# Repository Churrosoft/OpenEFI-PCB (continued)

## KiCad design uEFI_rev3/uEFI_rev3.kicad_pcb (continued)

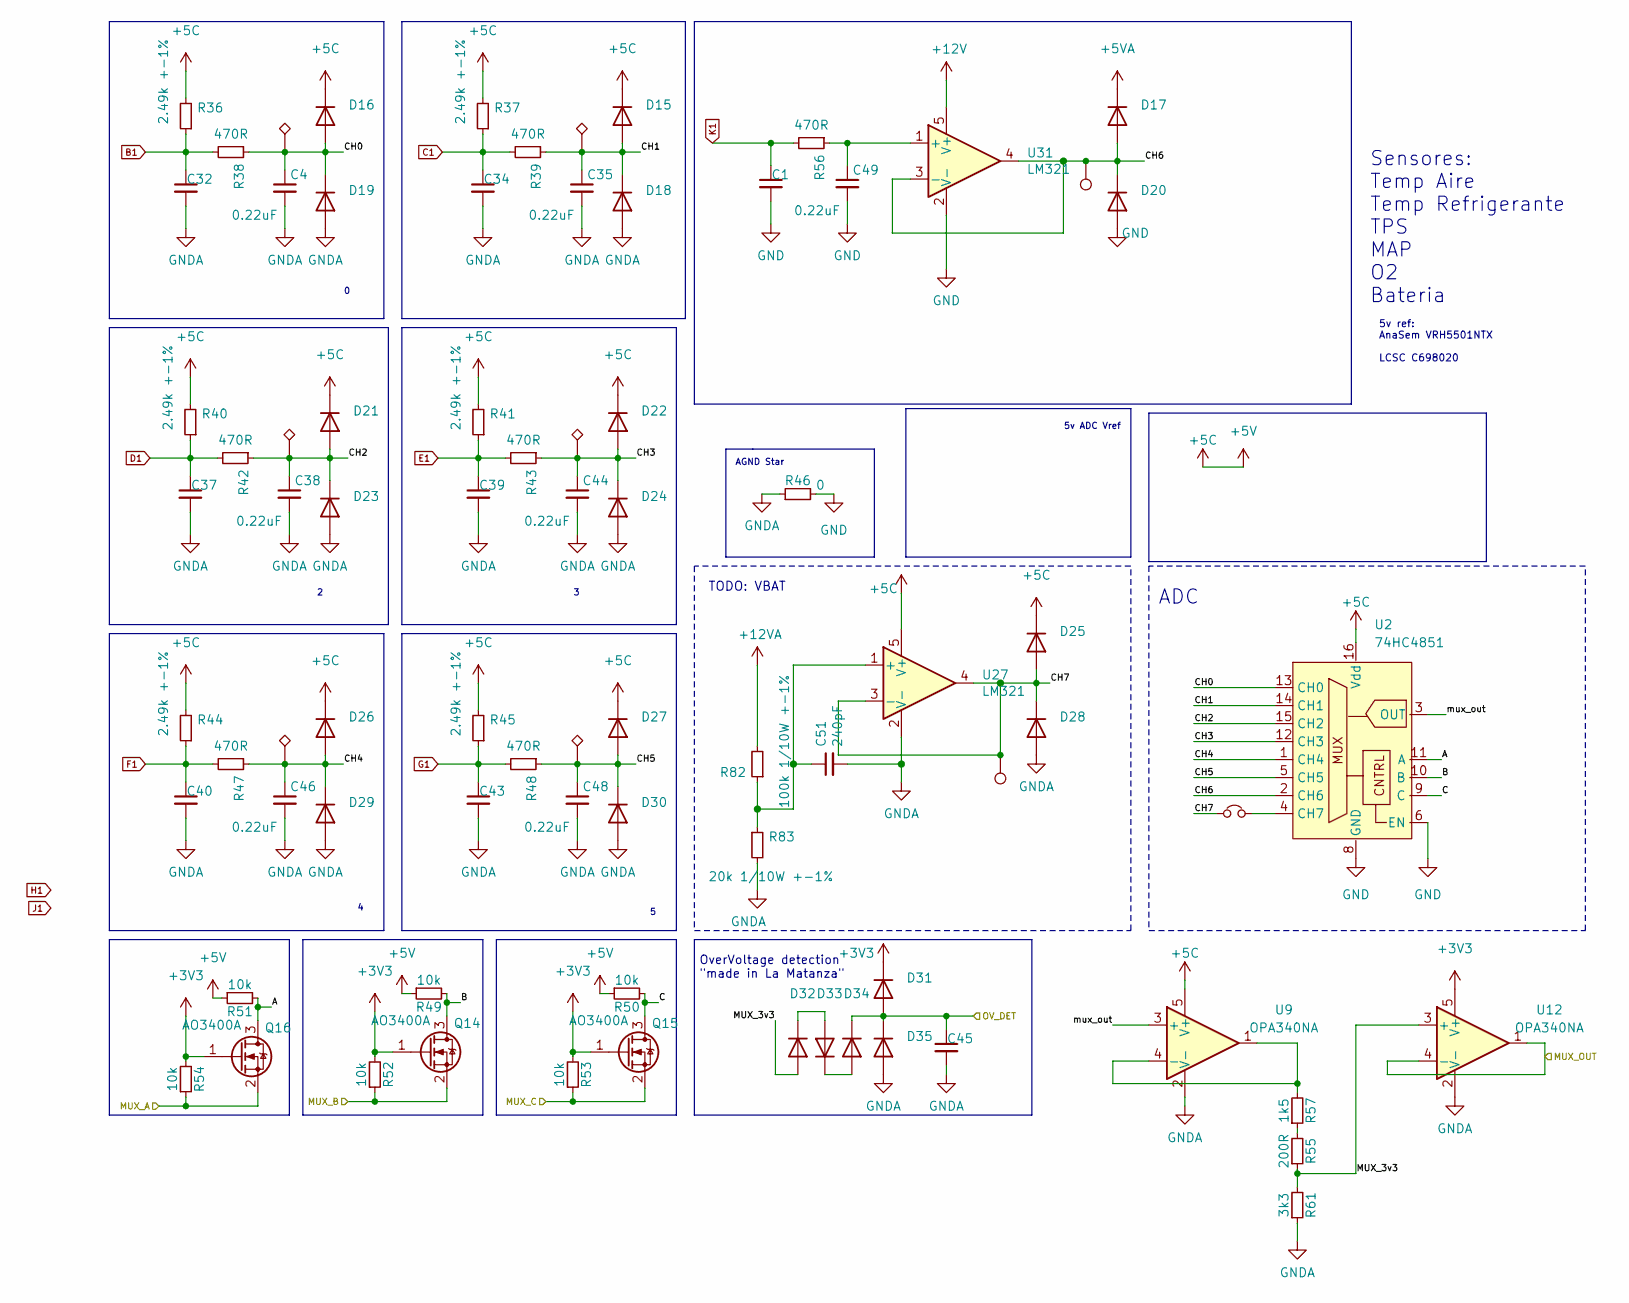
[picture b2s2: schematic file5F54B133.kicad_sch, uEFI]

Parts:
C1, C32, C34, C37, C39, C40, C43, C45: 100nF; C_0805_2012Metric; LCSC C49678
C4, C35, C38, C44, C46, C48, C49: 0.22uF; C_0603_1608Metric
C51: 240pF; C_0603_1608Metric; LCSC C185593
D15, D16, D17, D18, D19, D20, D21, D22, D23, D24, D25, D26, D27, D28, D29, D30, D31, D32, D33, D34, D35: K26; D_SOD-323; LCSC C2922179
JP12: Jumper_NC_Small; SolderJumper-2_P1.3mm_Open_TrianglePad1.0x1.5mm
Q14, Q15, Q16: AO3400A; SOT-23; LCSC C347475
R36, R37, R40, R41, R44, R45: 2.49k +-1%; R_0603_1608Metric
R38, R39, R42, R43, R47, R48, R56: 470R; R_0603_1608Metric
R46: 0; R_0603_1608Metric
R49, R50, R51, R52, R53, R54: 10k; R_0603_1608Metric
R55: 200R; R_0603_1608Metric
R57: 1k5; R_0603_1608Metric
R61: 3k3; R_0603_1608Metric
R82: 100k 1/10W +-1%; R_0603_1608Metric; LCSC C217840
R83: 20k 1/10W +-1%; R_0603_1608Metric
TP10, TP11, TP12, TP13, TP14, TP15: TestPoint_Alt; TestPoint_THTPad_1.0x1.0mm_Drill0.5mm
TP18, TP19: TestPoint; TestPoint_Pad_2.0x2.0mm
U2: 74HC4851; SOIC-16_3.9x9.9mm_P1.27mm; LCSC C233468
U9, U12: OPA340NA; SOT-23-5
U27, U31: LM321; SOT-23-5

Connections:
+5C: D15.1 (K), D16.1 (K), D21.1 (K), D22.1 (K), D25.1 (K), D26.1 (K), D27.1 (K), R36.2, R37.2, R40.2, R41.2, R44.2, R45.2, R49.1, R50.1, R51.1, U2.16 (Vdd), U9.5 (V+), U27.5 (V+); also elsewhere on the board
+5VA: D17.1 (K); also elsewhere on the board
+12V: U31.5 (V+); also elsewhere on the board
+12VA: R82.2; also elsewhere on the board
/MUX_A: Q16.2 (S), R54.1; also elsewhere on the board
/MUX_B: Q14.2 (S), R52.1; also elsewhere on the board
/MUX_C: Q15.2 (S), R53.1; also elsewhere on the board
/MUX_OUT: U12.1, U12.4 (-); also elsewhere on the board
/Sensores/A: Q16.3 (D), R51.2, U2.11 (A)
/Sensores/B: Q14.3 (D), R49.2, U2.10 (B)
/Sensores/C: Q15.3 (D), R50.2, U2.9 (C)
/Sensores/CH0: C4.1, D16.2 (A), D19.1 (K), R38.1, TP10.1, U2.13 (CH0)
/Sensores/CH1: C35.1, D15.2 (A), D18.1 (K), R39.1, TP11.1, U2.14 (CH1)
/Sensores/CH2: C38.1, D21.2 (A), D23.1 (K), R42.1, TP12.1, U2.15 (CH2)
/Sensores/CH3: C44.1, D22.2 (A), D24.1 (K), R43.1, TP13.1, U2.12 (CH3)
/Sensores/CH4: C46.1, D26.2 (A), D29.1 (K), R47.1, TP14.1, U2.1 (CH4)
/Sensores/CH5: C48.1, D27.2 (A), D30.1 (K), R48.1, TP15.1, U2.5 (CH5)
/Sensores/CH6: D17.2 (A), D20.1 (K), TP18.1, U2.2 (CH6), U31.3 (-), U31.4
/Sensores/CH7: D25.2 (A), D28.1 (K), JP12.1, TP19.1, U27.3 (-), U27.4
/Sensores/MUX_3v3: D32.2 (A), R55.1, R61.2, U12.3 (+)
/Sensores/mux_out: U2.3 (OUT), U9.3 (+)
B1: C32.1, R36.1, R38.2; also elsewhere on the board
C1: C34.1, R37.1, R39.2; also elsewhere on the board
D1: C37.1, R40.1, R42.2; also elsewhere on the board
E1: C39.1, R41.1, R43.2; also elsewhere on the board
F1: C40.1, R44.1, R47.2; also elsewhere on the board
G1: C43.1, R45.1, R48.2; also elsewhere on the board
GND: C1.2, C49.2, D20.2 (A), R46.2, U2.6 (EN), U2.8 (GND), U31.2 (V-); also elsewhere on the board
GNDA: C4.2, C32.2, C34.2, C35.2, C37.2, C38.2, C39.2, C40.2, C43.2, C44.2, C45.2, C46.2, C48.2, C51.2, D18.2 (A), D19.2 (A), D23.2 (A), D24.2 (A), D28.2 (A), D29.2 (A), D30.2 (A), D35.2 (A), R46.1, R61.1, R83.2, U9.2 (V-), U12.2 (V-), U27.2 (V-)
K1: C1.1, R56.2; also elsewhere on the board
unnamed: C45.1, D31.2 (A), D34.1 (K), D35.1 (K)
unnamed: C49.1, R56.1, U31.1 (+)
unnamed: C51.1, R82.1, R83.1, U27.1 (+)
unnamed: D32.1 (K), D33.2 (A)
unnamed: D33.1 (K), D34.2 (A)
unnamed: JP12.2, U2.4 (CH7)
unnamed: R55.2, R57.1
unnamed: R57.2, U9.1, U9.4 (-)

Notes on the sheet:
TODO: VBAT
Sensores: Temp Aire Temp Refrigerante TPS MAP O2 Bateria
OverVoltage detection "made in La Matanza"
ADC
5v ADC Vref
5v ref: AnaSem VRH5501NTX LCSC C698020
AGND Star

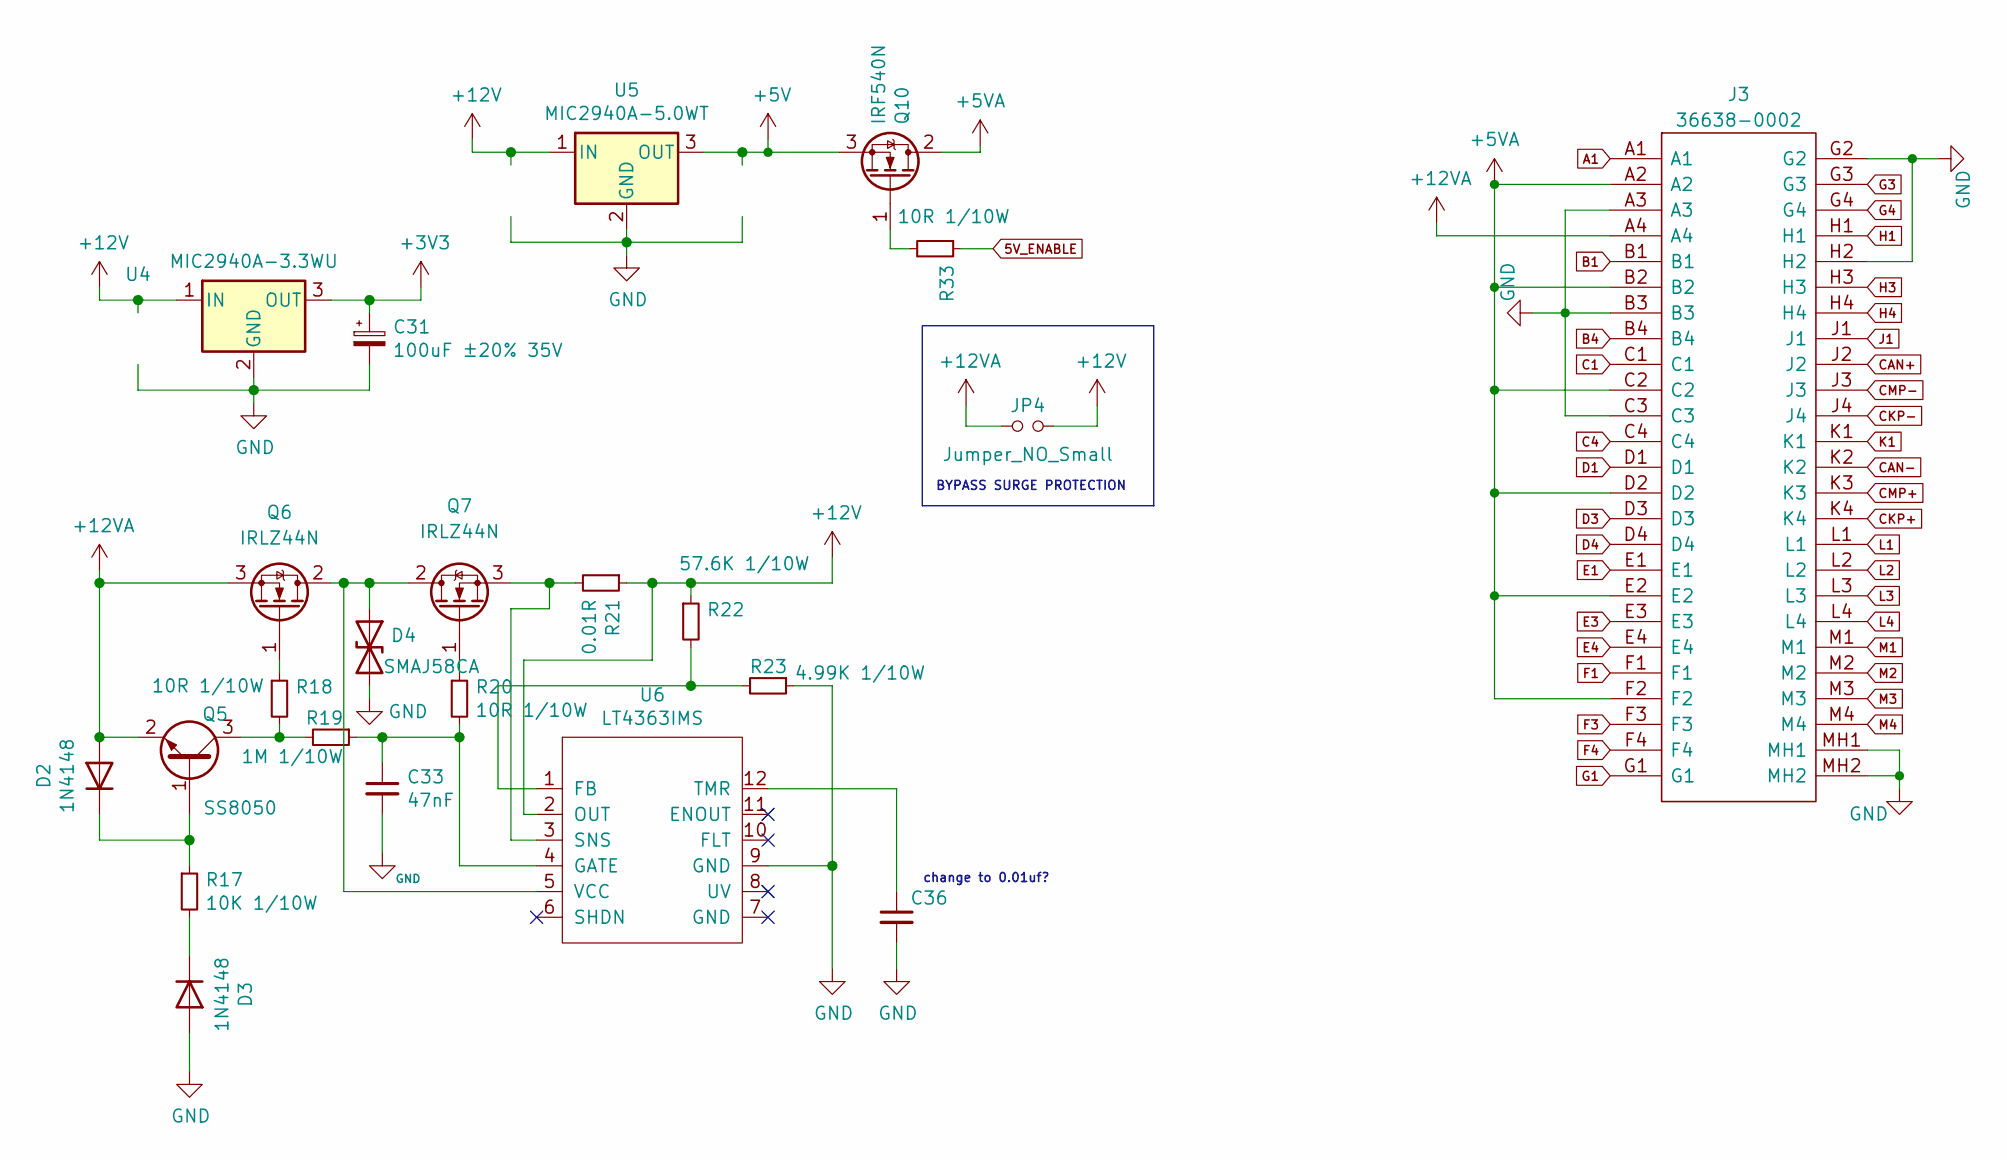
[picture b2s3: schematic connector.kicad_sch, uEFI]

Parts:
C31: 100uF ±20% 35V; CP_Elec_6.3x7.7; LCSC C141427
C33: 47nF; C_0603_1608Metric
C36: 100nF; C_0805_2012Metric; LCSC C49678
D2, D3: 1N4148; D_SOD-523; LCSC C511874
D4: SMAJ58CA; D_SMA
J3: 36638-0002; 366380002; Manufacturer_Part_Number 36638-0002; Mouser Part Number 538-36638-0002
JP4: Jumper_NO_Small; SolderJumper-2_P1.3mm_Open_RoundedPad1.0x1.5mm
Q5: SS8050; SOT-23; LCSC C2150
Q6, Q7: IRLZ44N; TO-220-3_Vertical
Q10: IRF540N; TO-220-3_Vertical
R17: 10K 1/10W; R_0603_1608Metric
R18, R20, R33: 10R 1/10W; R_0603_1608Metric
R19: 1M 1/10W; R_0603_1608Metric
R21: 0.01R; R_1210_3225Metric; LCSC C175884
R22: 57.6K 1/10W; R_0603_1608Metric
R23: 4.99K 1/10W; R_0603_1608Metric
U4: MIC2940A-3.3WU; TO-263-3_TabPin2
U5: MIC2940A-5.0WT; TO-220-3_Vertical
U6: LT4363IMS; MSOP-12_3x4mm_P0.65mm

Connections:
5V_ENABLE: R33.1; also elsewhere on the board
+5C: Q10.3 (S), U5.3 (OUT); also elsewhere on the board
+5VA: J3.A2, J3.B2, J3.C2, J3.D2, J3.E2, J3.F2, Q10.2 (D); also elsewhere on the board
+12V: JP4.2, R21.1, R22.1, U4.1 (IN), U5.1 (IN), U6.2 (OUT); also elsewhere on the board
+12VA: D2.2 (A), J3.A4, JP4.1, Q5.2 (E), Q6.3 (S); also elsewhere on the board
A1: J3.A1; also elsewhere on the board
B1: J3.B1; also elsewhere on the board
B4: J3.B4; also elsewhere on the board
C1: J3.C1; also elsewhere on the board
C4: J3.C4; also elsewhere on the board
CAN+: J3.J2; also elsewhere on the board
CAN-: J3.K2; also elsewhere on the board
CKP+: J3.K4; also elsewhere on the board
CKP-: J3.J4; also elsewhere on the board
CMP+: J3.K3; also elsewhere on the board
CMP-: J3.J3; also elsewhere on the board
D1: J3.D1; also elsewhere on the board
D3: J3.D3; also elsewhere on the board
D4: J3.D4; also elsewhere on the board
E1: J3.E1; also elsewhere on the board
E3: J3.E3; also elsewhere on the board
E4: J3.E4; also elsewhere on the board
F1: J3.F1; also elsewhere on the board
F3: J3.F3; also elsewhere on the board
F4: J3.F4; also elsewhere on the board
G1: J3.G1; also elsewhere on the board
G3: J3.G3; also elsewhere on the board
G4: J3.G4; also elsewhere on the board
GND: C31.2, C33.2, C36.2, D3.2 (A), D4.2 (A2), J3.A3, J3.B3, J3.C3, J3.G2, J3.H2, J3.MH1, J3.MH2, R23.1, U4.2 (GND), U5.2 (GND), U6.9 (GND); also elsewhere on the board
H1: J3.H1; also elsewhere on the board
H3: J3.H3; also elsewhere on the board
H4: J3.H4; also elsewhere on the board
J1: J3.J1
K1: J3.K1; also elsewhere on the board
L1: J3.L1; also elsewhere on the board
L2: J3.L2; also elsewhere on the board
L3: J3.L3; also elsewhere on the board
L4: J3.L4; also elsewhere on the board
M1: J3.M1; also elsewhere on the board
M2: J3.M2; also elsewhere on the board
M3: J3.M3; also elsewhere on the board
M4: J3.M4; also elsewhere on the board
unnamed: C33.1, R19.1, R20.2, U6.4 (GATE)
unnamed: C36.1, U6.12 (TMR)
unnamed: D2.1 (K), Q5.1 (B), R17.1
unnamed: D3.1 (K), R17.2
unnamed: D4.1 (A1), Q6.2 (D), Q7.2 (D), U6.5 (VCC)
unnamed: Q5.3 (C), R18.2, R19.2
unnamed: Q6.1 (G), R18.1
unnamed: Q7.1 (G), R20.1
unnamed: Q7.3 (S), R21.2, U6.3 (SNS)
unnamed: Q10.1 (G), R33.2
unnamed: R22.2, R23.2, U6.1 (FB)

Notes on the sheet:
BYPASS SURGE PROTECTION
change to 0.01uf?

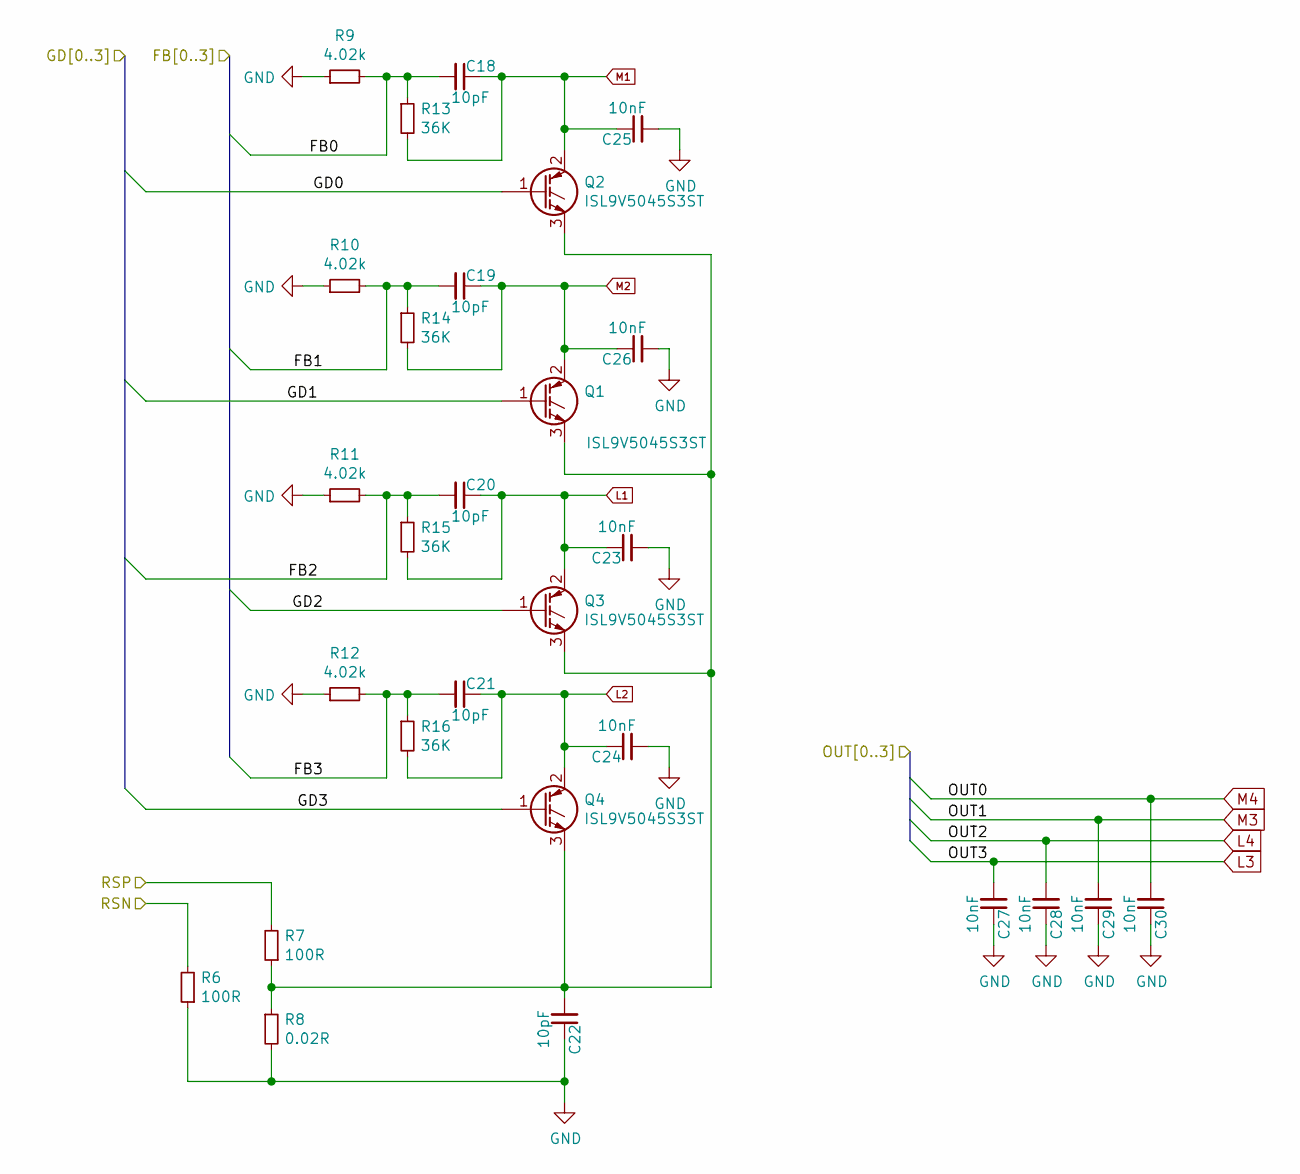
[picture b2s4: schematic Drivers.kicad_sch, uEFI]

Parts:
C18, C19, C20, C21: 10pF; C_0603_1608Metric; LCSC C106245
C22: 10pF; C_0603_1608Metric
C23, C24, C25, C26, C27, C28, C29, C30: 10nF; C_0603_1608Metric; LCSC C100042
Q1, Q2, Q3, Q4: ISL9V5045S3ST; TO-263-2
R6, R7: 100R; R_0603_1608Metric; LCSC C159890
R8: 0.02R; R_2512_6332Metric; LCSC C326611
R9, R10, R11, R12: 4.02k; R_0603_1608Metric; LCSC C23040
R13, R14, R15, R16: 36K; R_0603_1608Metric; LCSC C192548

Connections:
/RSN: R6.2; also elsewhere on the board
/RSP: R7.2; also elsewhere on the board
/Sheet5FA9324A/FB0: C18.2, R9.2, R13.1; also elsewhere on the board
/Sheet5FA9324A/FB1: C19.2, R10.2, R14.1; also elsewhere on the board
/Sheet5FA9324A/FB2: C20.2, R11.2, R15.1; also elsewhere on the board
/Sheet5FA9324A/FB3: C21.2, R12.2, R16.1; also elsewhere on the board
/Sheet5FA9324A/GD0: Q2.1 (G); also elsewhere on the board
/Sheet5FA9324A/GD1: Q1.1 (G); also elsewhere on the board
/Sheet5FA9324A/GD2: Q3.1 (G); also elsewhere on the board
/Sheet5FA9324A/GD3: Q4.1 (G); also elsewhere on the board
GND: C22.1, C23.2, C24.2, C25.2, C26.2, C27.1, C28.1, C29.1, C30.1, R6.1, R8.2, R9.1, R10.1, R11.1, R12.1; also elsewhere on the board
L1: C20.1, C23.1, Q3.2 (C), R15.2; also elsewhere on the board
L2: C21.1, C24.1, Q4.2 (C), R16.2; also elsewhere on the board
L3: C27.2; also elsewhere on the board
L4: C28.2; also elsewhere on the board
M1: C18.1, C25.1, Q2.2 (C), R13.2; also elsewhere on the board
M2: C19.1, C26.1, Q1.2 (C), R14.2; also elsewhere on the board
M3: C29.2; also elsewhere on the board
M4: C30.2; also elsewhere on the board
unnamed: C22.2, Q1.3 (E), Q2.3 (E), Q3.3 (E), Q4.3 (E), R7.1, R8.1

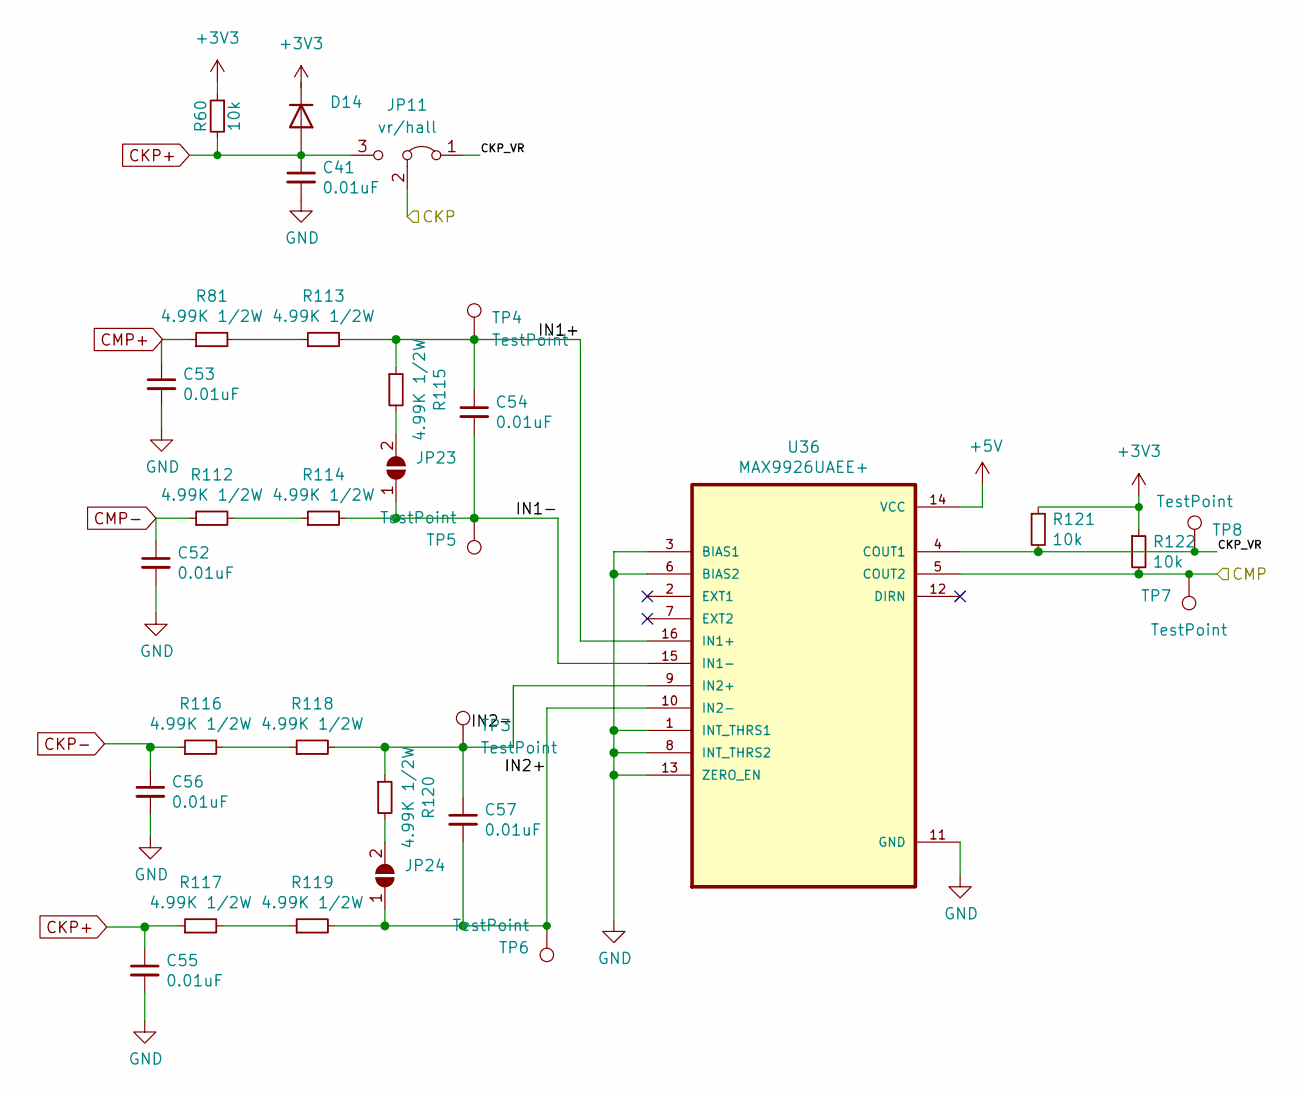
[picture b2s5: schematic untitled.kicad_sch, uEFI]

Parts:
C41, C52, C53, C54, C55, C56, C57: 0.01uF; C_0805_2012Metric; LCSC C100042
D14: K26; D_SOD-323; LCSC C2922179
JP11: vr/hall; SolderJumper-3_P1.3mm_Bridged2Bar12_Pad1.0x1.5mm_NumberLabe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
JP23, JP24: SolderJumper_2_Open; SolderJumper-2_P1.3mm_Open_RoundedPad1.0x1.5mm
R60, R121, R122: 10k; R_0603_1608Metric
R81, R112, R113, R114, R115, R116, R117, R118, R119, R120: 4.99K 1/2W; R_1210_3225Metric; LCSC C407178
TP3, TP4, TP5, TP6, TP7, TP8: TestPoint; TestPoint_Pad_1.0x1.0mm
U36: MAX9926UAEE+; SOP63P602X175-16N

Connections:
+5C: U36.14 (VCC); also elsewhere on the board
/CKP: JP11.2 (C); also elsewhere on the board
/CKP/CMP_sensors/CKP_VR: JP11.1 (A), R121.2, TP8.1, U36.4 (COUT1)
/CKP/CMP_sensors/IN1+: C54.1, R113.2, R115.1, TP4.1, U36.16 (IN1+)
/CKP/CMP_sensors/IN1-: C54.2, JP23.1 (A), R114.2, TP5.1, U36.15 (IN1-)
/CKP/CMP_sensors/IN2+: C57.2, JP24.1 (A), R119.2, TP6.1, U36.10 (IN2-)
/CKP/CMP_sensors/IN2-: C57.1, R118.2, R120.1, TP3.1, U36.9 (IN2+)
/CMP: R122.2, TP7.1, U36.5 (COUT2); also elsewhere on the board
CKP+: C41.1, C55.1, D14.2 (A), JP11.3 (B), R60.2, R117.1; also elsewhere on the board
CKP-: C56.1, R116.1; also elsewhere on the board
CMP+: C53.1, R81.1; also elsewhere on the board
CMP-: C52.1, R112.1; also elsewhere on the board
GND: C41.2, C52.2, C53.2, C55.2, C56.2, U36.1 (INT_THRS1), U36.3 (BIAS1), U36.6 (BIAS2), U36.8 (INT_THRS2), U36.11 (GND), U36.13 (ZERO_EN); also elsewhere on the board
unnamed: JP23.2 (B), R115.2
unnamed: JP24.2 (B), R120.2
unnamed: R112.2, R114.1
unnamed: R81.2, R113.1
unnamed: R116.2, R118.1
unnamed: R117.2, R119.1

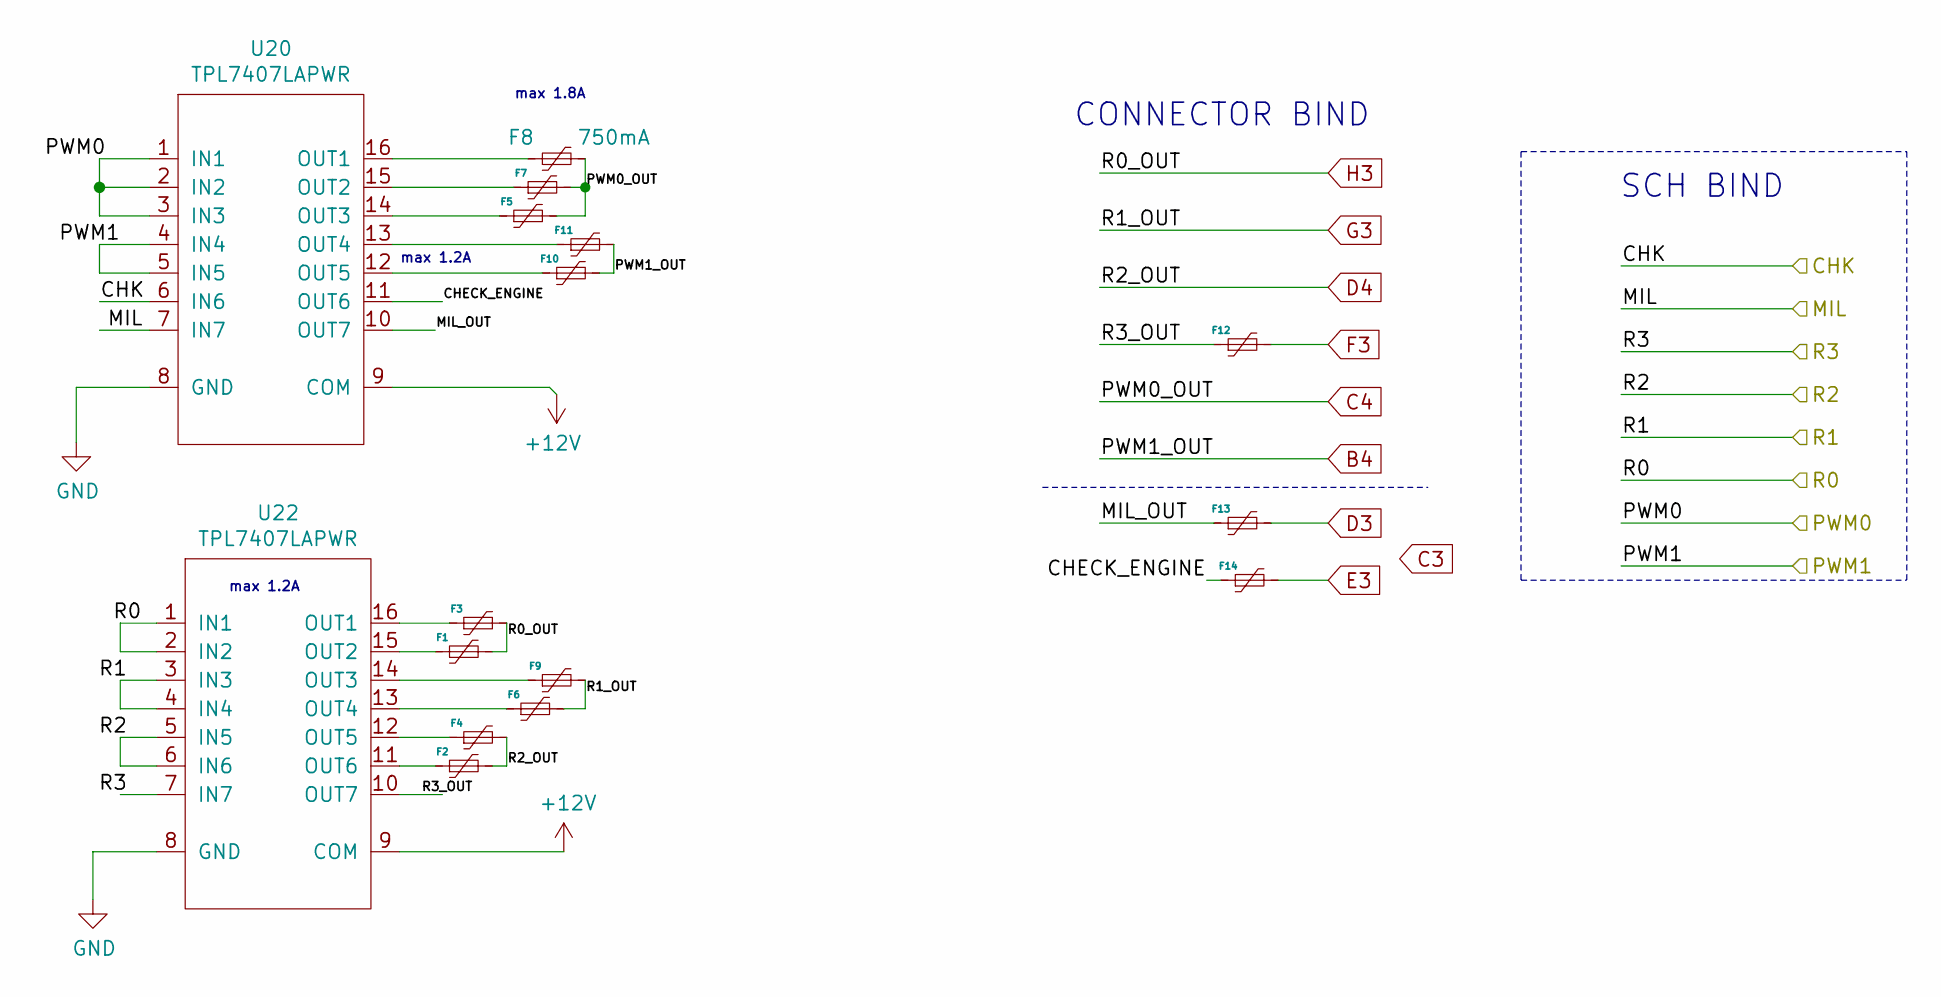
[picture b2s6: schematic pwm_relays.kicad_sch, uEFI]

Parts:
F1, F2, F3, F4, F5, F6, F7, F8, F9, F10, F11, F12, F13, F14: 750mA; Fuse_0805_2012Metric; LCSC C2760263
U20, U22: TPL7407LAPWR; TSSOP-16_4.4x5mm_P0.65mm; LCSC C91443

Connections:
+12V: U20.9 (COM), U22.9 (COM); also elsewhere on the board
/CHK_OUT: U20.6 (IN6); also elsewhere on the board
/MIL_OUT: U20.7 (IN7); also elsewhere on the board
/PWM/Relays/CHECK_ENGINE: F14.1, U20.11 (OUT6)
/PWM/Relays/MIL_OUT: F13.1, U20.10 (OUT7)
/PWM/Relays/R3_OUT: F12.1, U22.10 (OUT7)
/R_AAC: U22.1 (IN1), U22.2 (IN2); also elsewhere on the board
/R_ECN_INY: U22.5 (IN5), U22.6 (IN6); also elsewhere on the board
/R_GNC_GLP: U22.3 (IN3), U22.4 (IN4); also elsewhere on the board
/R_LMB: U22.7 (IN7); also elsewhere on the board
/TIM9_CH1: U20.1 (IN1), U20.2 (IN2), U20.3 (IN3); also elsewhere on the board
/TIM9_CH2: U20.4 (IN4), U20.5 (IN5); also elsewhere on the board
B4: F10.2, F11.2; also elsewhere on the board
C4: F5.2, F7.2, F8.2; also elsewhere on the board
D3: F13.2; also elsewhere on the board
D4: F2.2, F4.2; also elsewhere on the board
E3: F14.2; also elsewhere on the board
F3: F12.2; also elsewhere on the board
G3: F6.2, F9.2; also elsewhere on the board
GND: U20.8 (GND), U22.8 (GND); also elsewhere on the board
H3: F1.2, F3.2; also elsewhere on the board
unnamed: F1.1, U22.15 (OUT2)
unnamed: F2.1, U22.11 (OUT6)
unnamed: F3.1, U22.16 (OUT1)
unnamed: F4.1, U22.12 (OUT5)
unnamed: F5.1, U20.14 (OUT3)
unnamed: F6.1, U22.13 (OUT4)
unnamed: F7.1, U20.15 (OUT2)
unnamed: F8.1, U20.16 (OUT1)
unnamed: F9.1, U22.14 (OUT3)
unnamed: F10.1, U20.12 (OUT5)
unnamed: F11.1, U20.13 (OUT4)

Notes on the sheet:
max 1.8A
max 1.2A
SCH BIND
CONNECTOR BIND

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
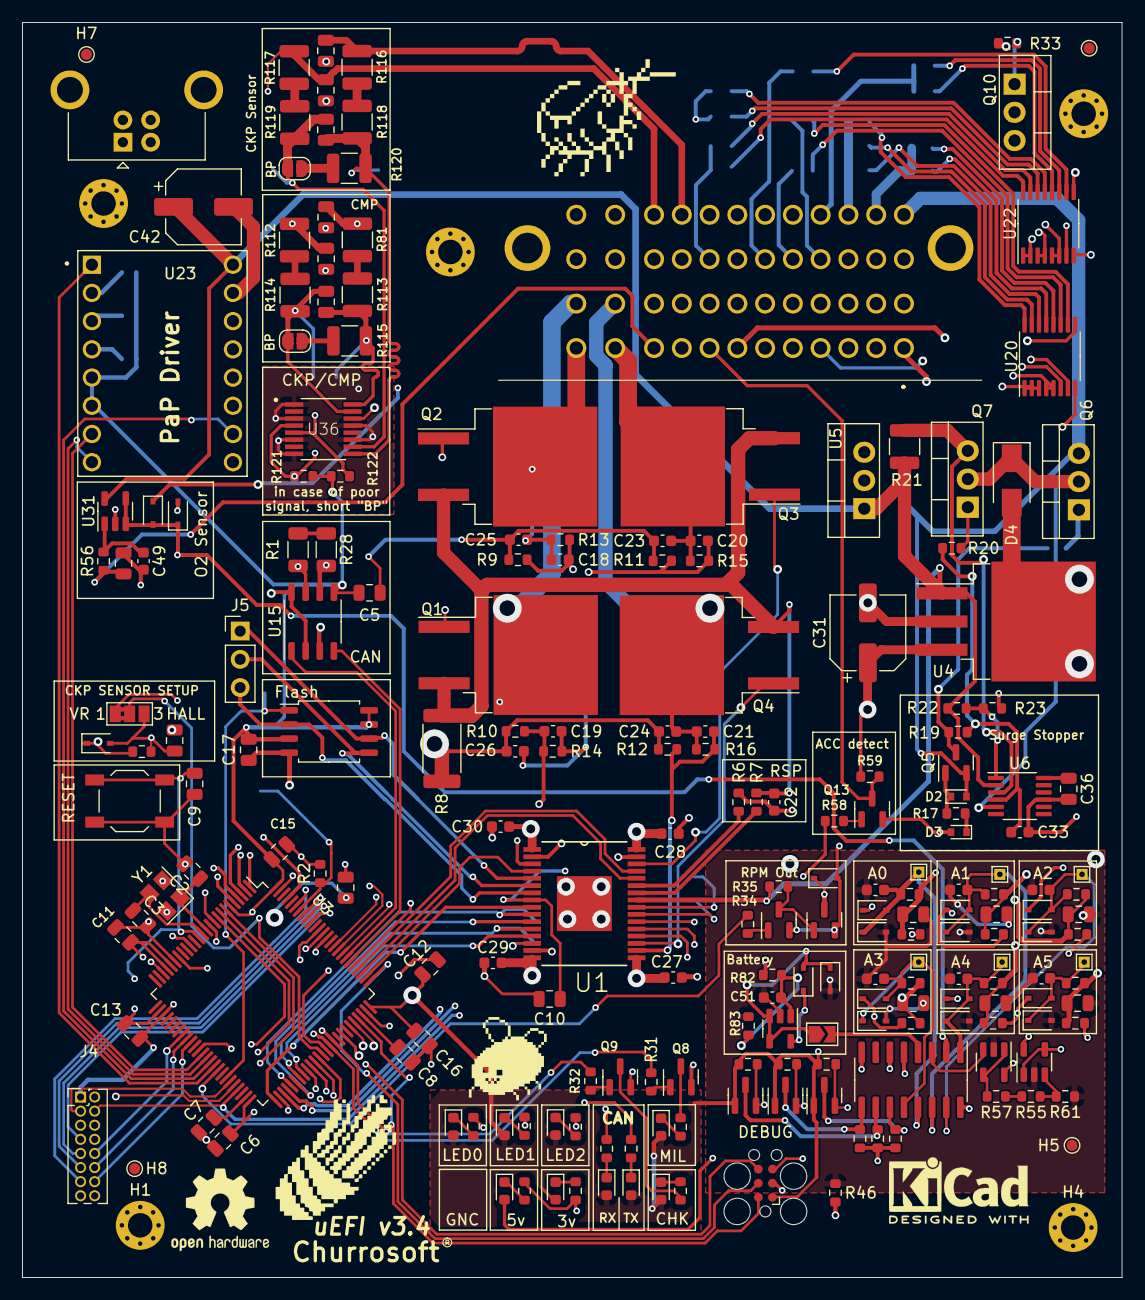
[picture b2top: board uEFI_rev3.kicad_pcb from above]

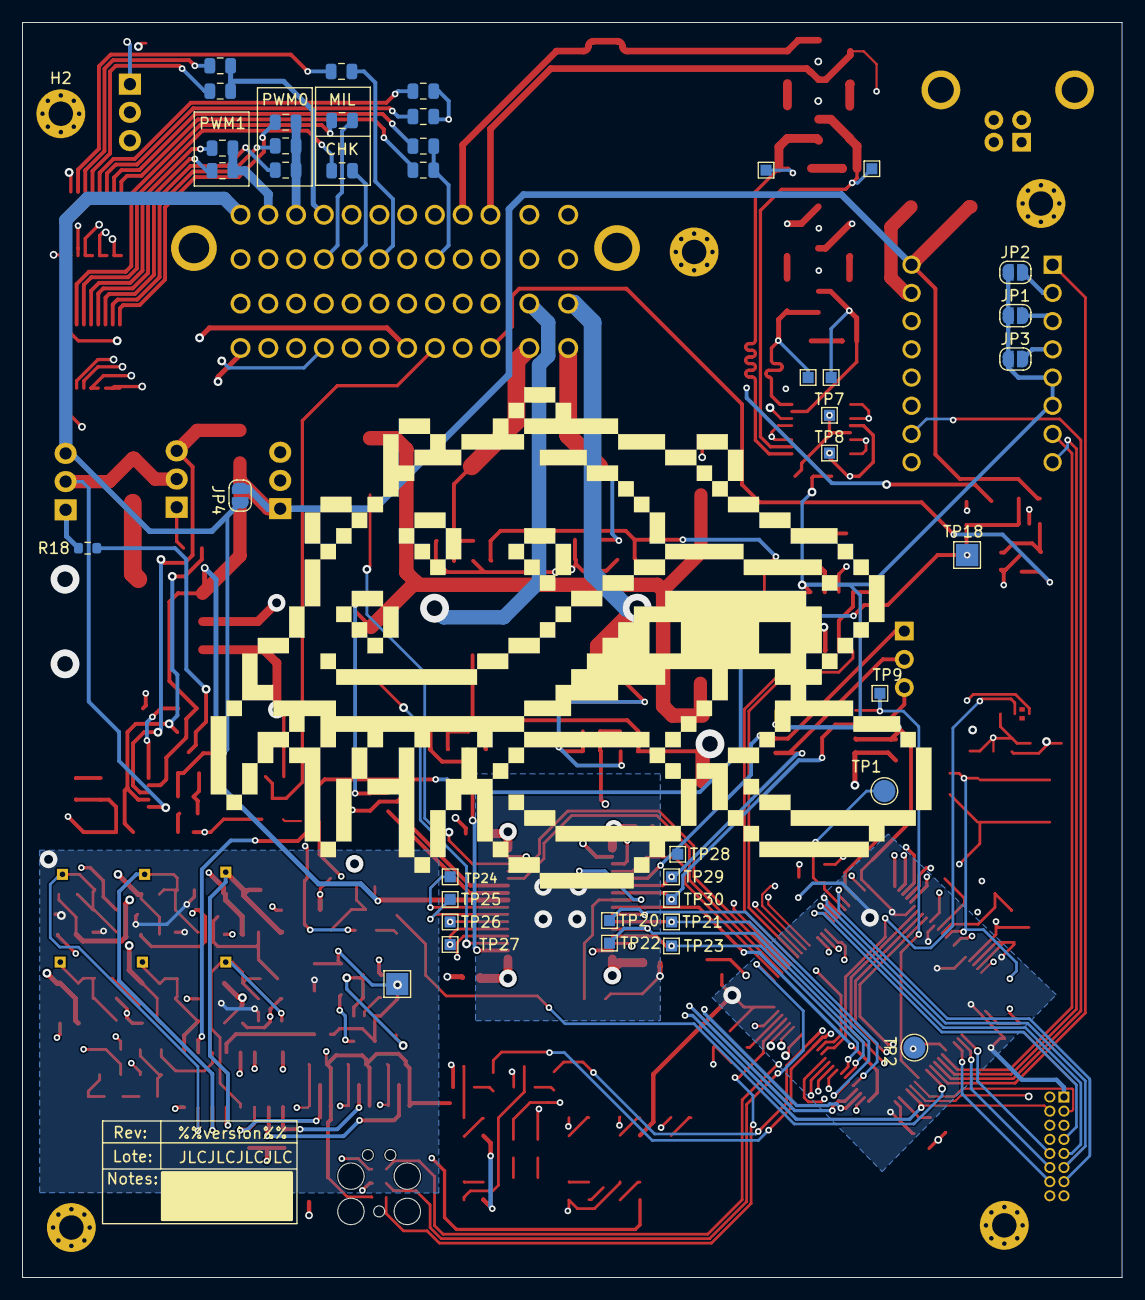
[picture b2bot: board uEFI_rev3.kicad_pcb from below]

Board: 4 copper layers, 99.0 x 113.0 mm, 260 parts (42 on the bottom side), 194 nets.

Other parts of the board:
Churrosoft: SYM_Hot_Large; churro_new_v4

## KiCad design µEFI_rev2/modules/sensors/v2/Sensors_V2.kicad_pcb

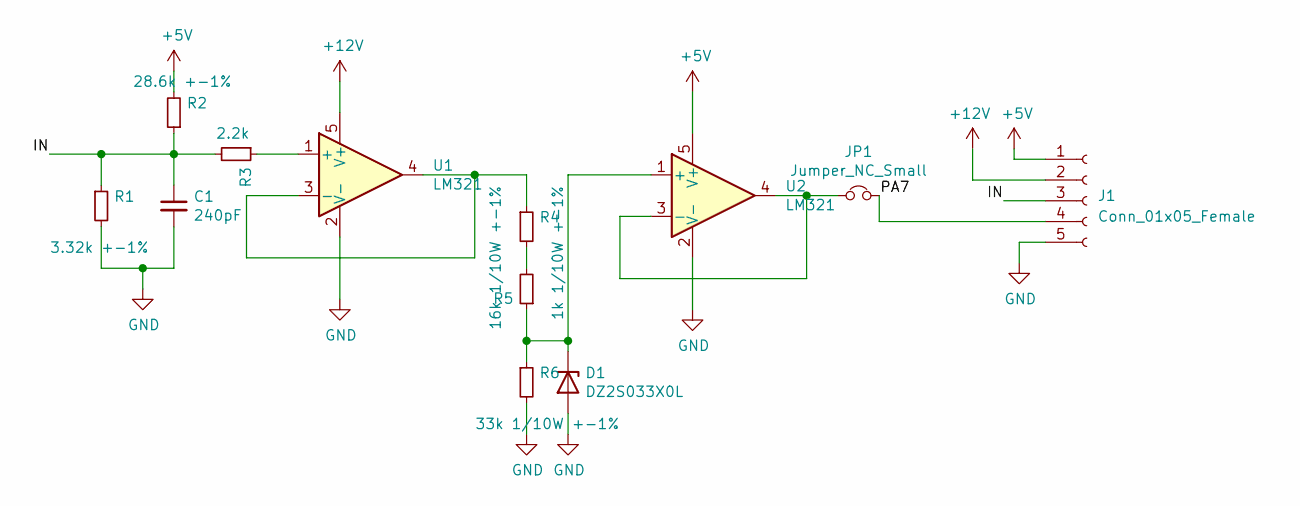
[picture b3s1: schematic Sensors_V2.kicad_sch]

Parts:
C1: 240pF; C_0603_1608Metric; LCSC C185593
D1: DZ2S033X0L; D_MiniMELF; LCSC C8056
J1: Conn_01x05_Female; PinHeader_1x05_P1.27mm_Horizontal
JP1: Jumper_NC_Small; SolderJumper-2_P1.3mm_Open_TrianglePad1.0x1.5mm
R1: 3.32k +-1%; R_0603_1608Metric; LCSC C234508
R2: 28.6k +-1%; R_0603_1608Metric; LCSC C217931
R3: 2.2k; R_0603_1608Metric; LCSC C309092
R4: 16k 1/10W +-1%; R_0603_1608Metric; LCSC C217760
R5: 1k 1/10W +-1%; R_0603_1608Metric; LCSC C217840
R6: 33k 1/10W +-1%; R_0603_1608Metric
U1, U2: LM321; SOT-23-5

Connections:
+5V: J1.1, R2.2, U2.5 (V+)
+12V: J1.2, U1.5 (V+)
/IN: C1.1, J1.3, R1.1, R2.1, R3.2
GND: C1.2, D1.2 (A), J1.5, R1.2, R6.2, U1.2 (V-), U2.2 (V-)
unnamed: D1.1 (K), R5.1, R6.1, U2.1 (+)
unnamed: J1.4, JP1.2
unnamed: JP1.1, U2.3 (-), U2.4
unnamed: R3.1, U1.1 (+)
unnamed: R4.1, U1.3 (-), U1.4
unnamed: R4.2, R5.2

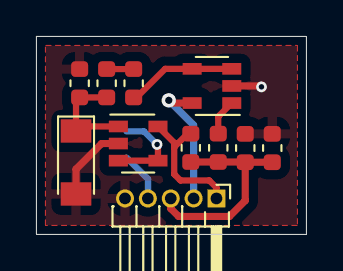
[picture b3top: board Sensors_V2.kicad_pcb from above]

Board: 2 copper layers, 15.0 x 11.0 mm, 12 parts (1 on the bottom side), 10 nets.
